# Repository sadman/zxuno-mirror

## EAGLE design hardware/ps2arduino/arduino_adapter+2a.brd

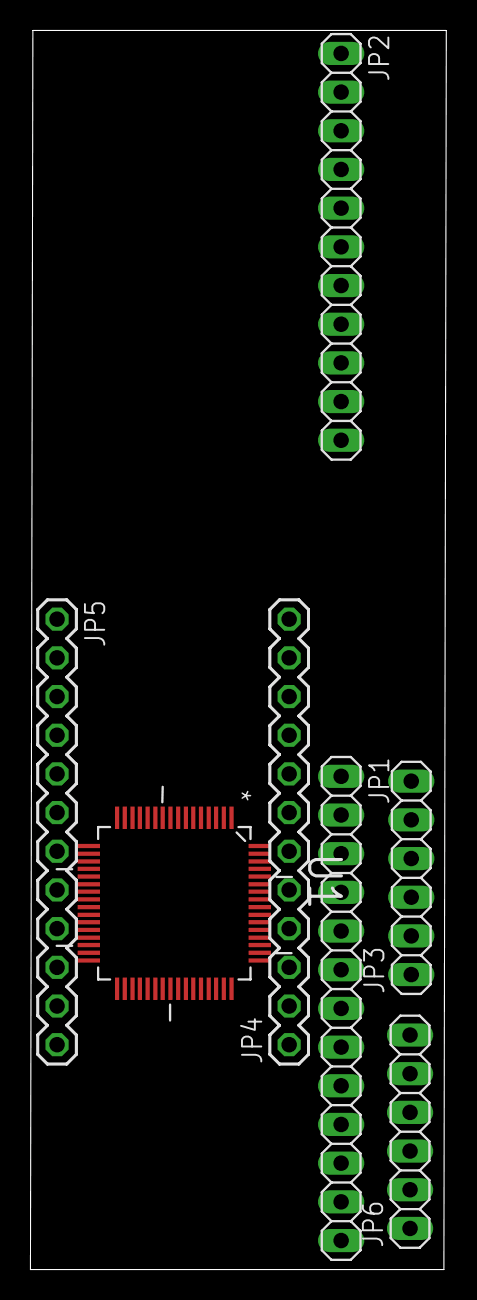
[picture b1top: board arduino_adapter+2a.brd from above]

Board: 2 copper layers, 27.3 x 81.4 mm, 7 parts (0 on the bottom side), 19 nets, no tracks yet.

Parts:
JP1: 1X13
JP2: 1X11
JP3, JP6: 1X06
JP4, JP5: 1X12
U1: STM32F105RBT6; QFP50P1200X1200X160-64N

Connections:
A8: JP1.6, JP4.3
A9: JP1.3, JP4.6
A10: JP1.2, JP4.7
A11: JP1.1, JP4.8
A12: JP1.4, JP4.5
A13: JP1.5, JP4.4
A14: JP1.7, JP4.2
A15: JP1.8, JP4.1
D0: JP2.1, JP5.7
D1: JP2.2, JP5.8
D2: JP2.3, JP5.10
D3: JP2.4, JP5.11
D4: JP2.5, JP5.12
GND: JP3.3, JP5.2, JP6.3
unnamed: JP3.6, JP6.5
unnamed: JP3.2, JP6.1
PS2_CLK: JP3.5, JP5.6
PS2_DATA: JP3.1, JP5.5
VCC: JP3.4, JP5.1, JP6.4

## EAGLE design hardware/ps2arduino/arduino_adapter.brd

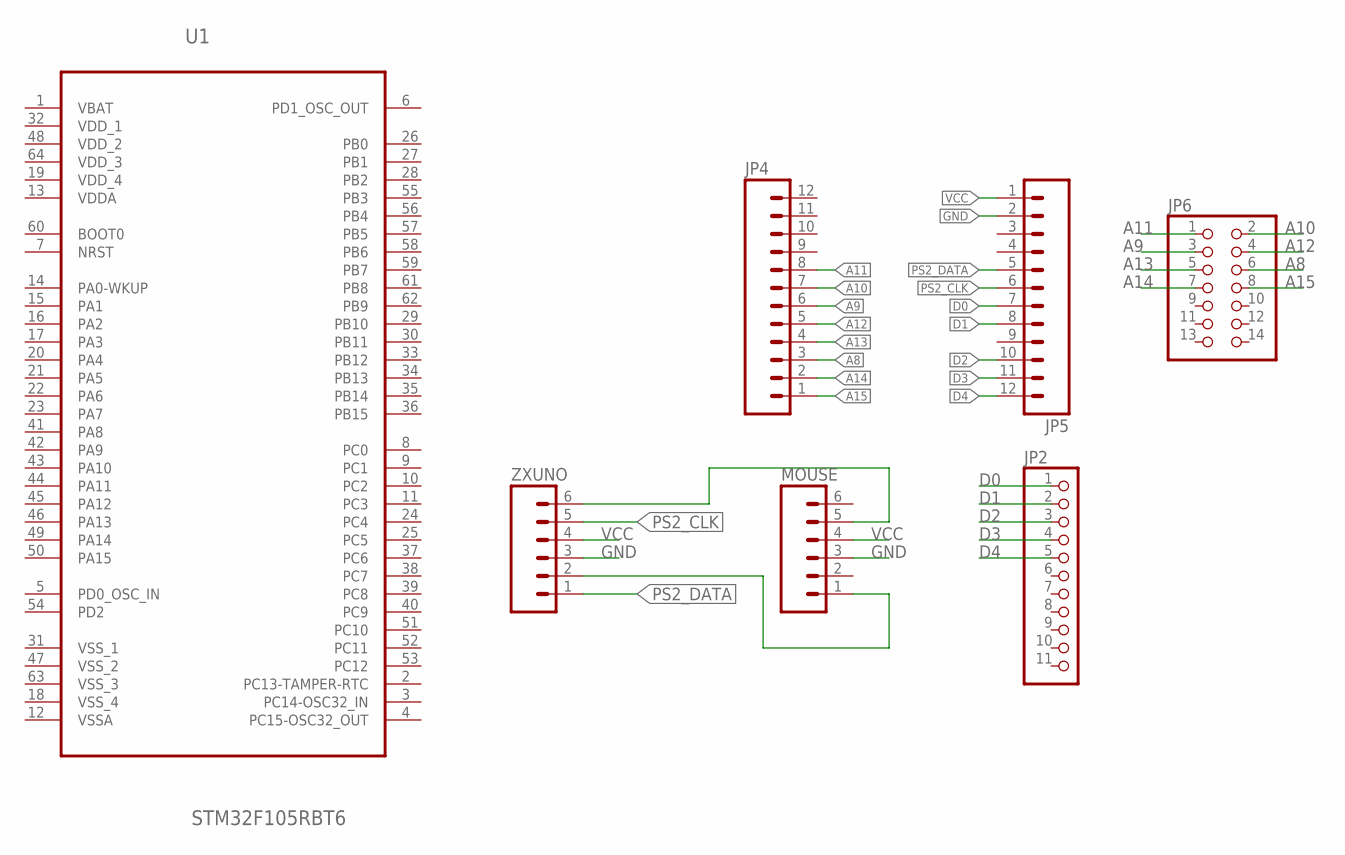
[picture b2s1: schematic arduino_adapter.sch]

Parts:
JP2: PINHD-1X11; 1X11
JP4, JP5: M12PTH; 1X12
JP6: PINHD-2X7; 2X07
MOUSE: DINC_MIN_TM_6_1; DINC/MIN_TM/6_1PRIMARY
U1: STM32F105RBT6; QFP50P1200X1200X160-64N
ZXUNO: DINC_MIN_TM_6_1; DINC/MIN_TM/6_1PRIMARY

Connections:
A8: JP4.3, JP6.6
A9: JP4.6, JP6.3
A10: JP4.7, JP6.2
A11: JP4.8, JP6.1
A12: JP4.5, JP6.4
A13: JP4.4, JP6.5
A14: JP4.2, JP6.7
A15: JP4.1, JP6.8
D0: JP2.1, JP5.7
D1: JP2.2, JP5.8
D2: JP2.3, JP5.10
D3: JP2.4, JP5.11
D4: JP2.5, JP5.12
GND: JP5.2, MOUSE.3, ZXUNO.3
unnamed: MOUSE.5, ZXUNO.6
unnamed: MOUSE.1, ZXUNO.2
PS2_CLK: JP5.6, ZXUNO.5
PS2_DATA: JP5.5, ZXUNO.1
VBAT: U1.1 (VBAT)
VCC: JP5.1, MOUSE.4, ZXUNO.4
VDDA: U1.13 (VDDA)
VDD_1: U1.32 (VDD_1)
VDD_2: U1.48 (VDD_2)
VDD_3: U1.64 (VDD_3)
VDD_4: U1.19 (VDD_4)
VSSA: U1.12 (VSSA)
VSS_1: U1.31 (VSS_1)
VSS_2: U1.47 (VSS_2)
VSS_3: U1.63 (VSS_3)
VSS_4: U1.18 (VSS_4)

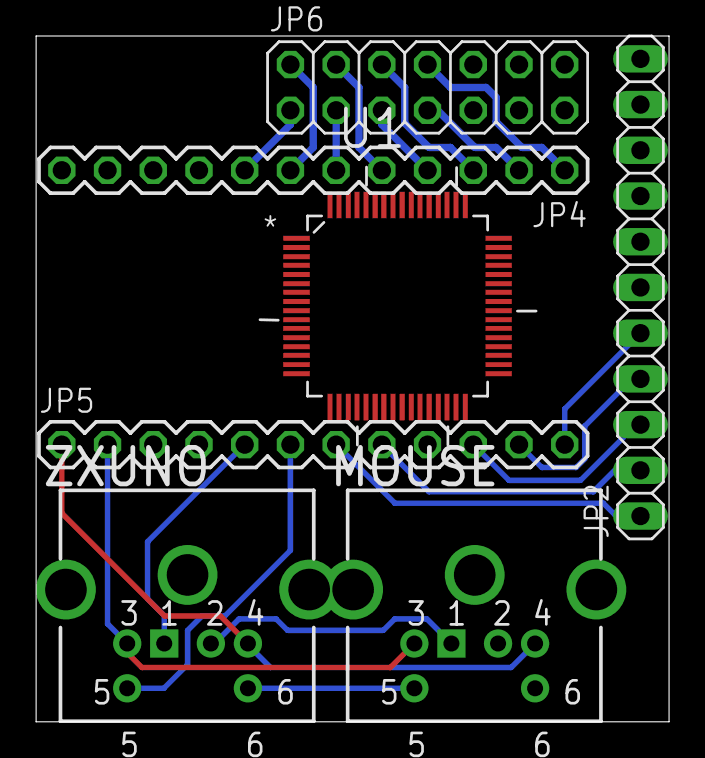
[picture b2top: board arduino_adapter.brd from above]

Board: 2 copper layers, 35.2 x 38.1 mm, 7 parts (0 on the bottom side), 19 nets.

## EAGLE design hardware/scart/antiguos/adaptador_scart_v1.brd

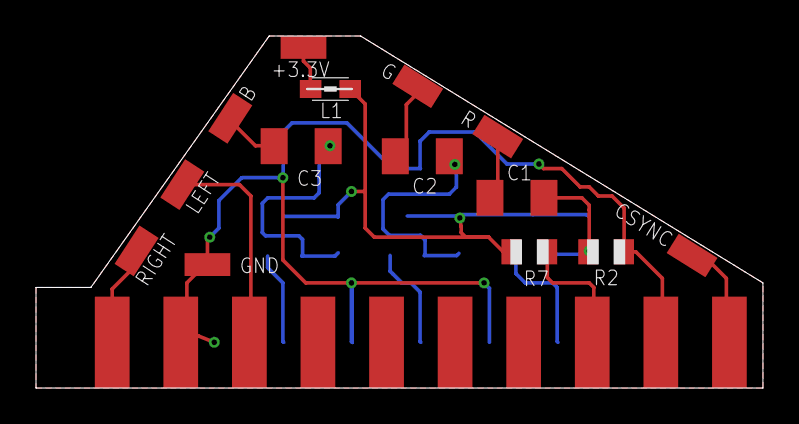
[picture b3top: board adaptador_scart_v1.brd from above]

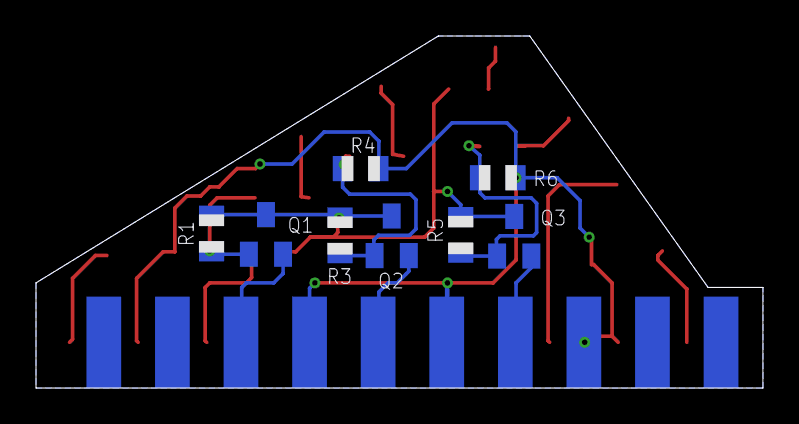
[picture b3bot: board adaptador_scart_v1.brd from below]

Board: 2 copper layers, 40.4 x 19.6 mm, 23 parts (9 on the bottom side), 16 nets.

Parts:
+3.3V: SMD1,27-2,54
B: SMD1,27-2,54
C1, C2, C3: 1uF; C1206K
CSYNC: SMD1,27-2,54
G: SMD1,27-2,54
GND: SMD1,27-2,54
L1: 0805
LEFT: SMD1,27-2,54
Q1, Q2, Q3: 2N3904; SOT23
R: SMD1,27-2,54
R1, R3, R5: 10K; R0805
R2, R4, R6: 22K; R0805
R7: 50; R0805
RIGHT: SMD1,27-2,54
U$1: SCART-MALE-PCB; SCART-PCB

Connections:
BIN: B.1, C3.1
BOUT: Q3.2, U$1.7
CSYNC: CSYNC.1, U$1.20
FS: R7.1, U$1.16
GIN: C2.1, G.1
GND: GND.1, R2.1, R4.1, R6.1, U$1.4, U$1.5, U$1.9, U$1.13, U$1.18
GOUT: Q2.2, U$1.11
LEFT: LEFT.1, U$1.6
unnamed: C1.2, Q1.1, R1.1, R2.2
unnamed: C3.2, Q3.1, R5.1, R6.2
unnamed: C2.2, Q2.1, R3.1, R4.2
RIGHT: RIGHT.1, U$1.2
RIN: C1.1, R.1
ROUT: Q1.2, U$1.15
VCC: L1.2, Q1.3, Q2.3, Q3.3, R1.2, R3.2, R5.2, R7.2
VCCIN: +3.3V.1, L1.1

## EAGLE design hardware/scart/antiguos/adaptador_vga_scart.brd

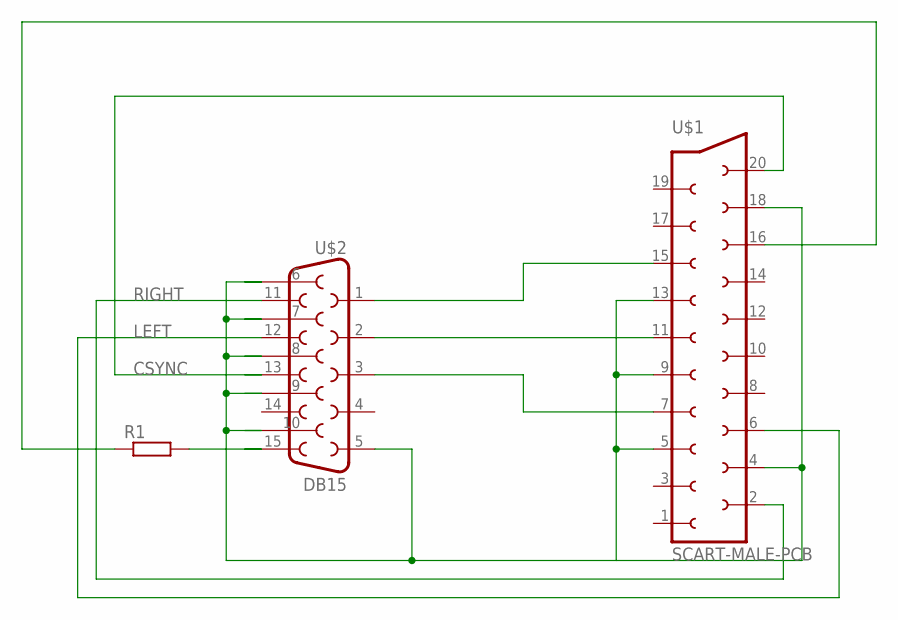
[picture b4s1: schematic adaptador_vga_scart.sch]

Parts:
R1: R-EU_0204/7; 0204/7
U$1: SCART-MALE-PCB; SCART-PCB
U$2: DB15

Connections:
BOUT: U$1.7, U$2.3
CSYNC: U$1.20, U$2.13
GND: U$1.4, U$1.5, U$1.9, U$1.13, U$1.18, U$2.5, U$2.6, U$2.7, U$2.8, U$2.9, U$2.10
GOUT: U$1.11, U$2.2
LEFT: U$1.6, U$2.12
unnamed: U$1.15, U$2.1
unnamed: R1.2, U$2.15
unnamed: R1.1, U$1.16
RIGHT: U$1.2, U$2.11

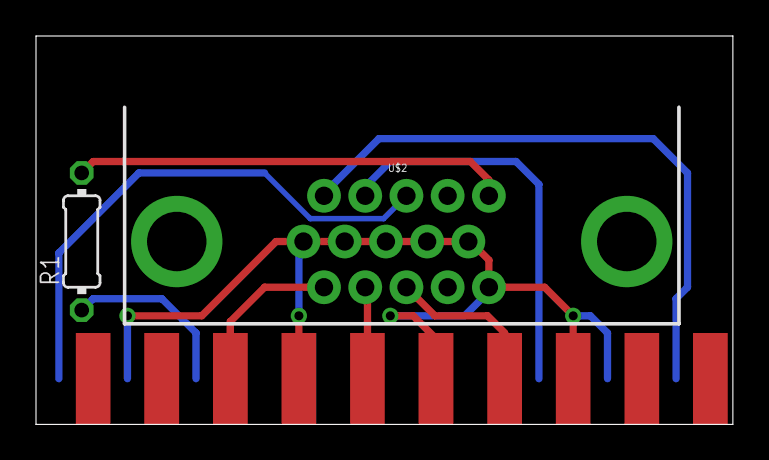
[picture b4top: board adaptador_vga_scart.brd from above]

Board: 2 copper layers, 38.7 x 21.6 mm, 3 parts (0 on the bottom side), 9 nets.

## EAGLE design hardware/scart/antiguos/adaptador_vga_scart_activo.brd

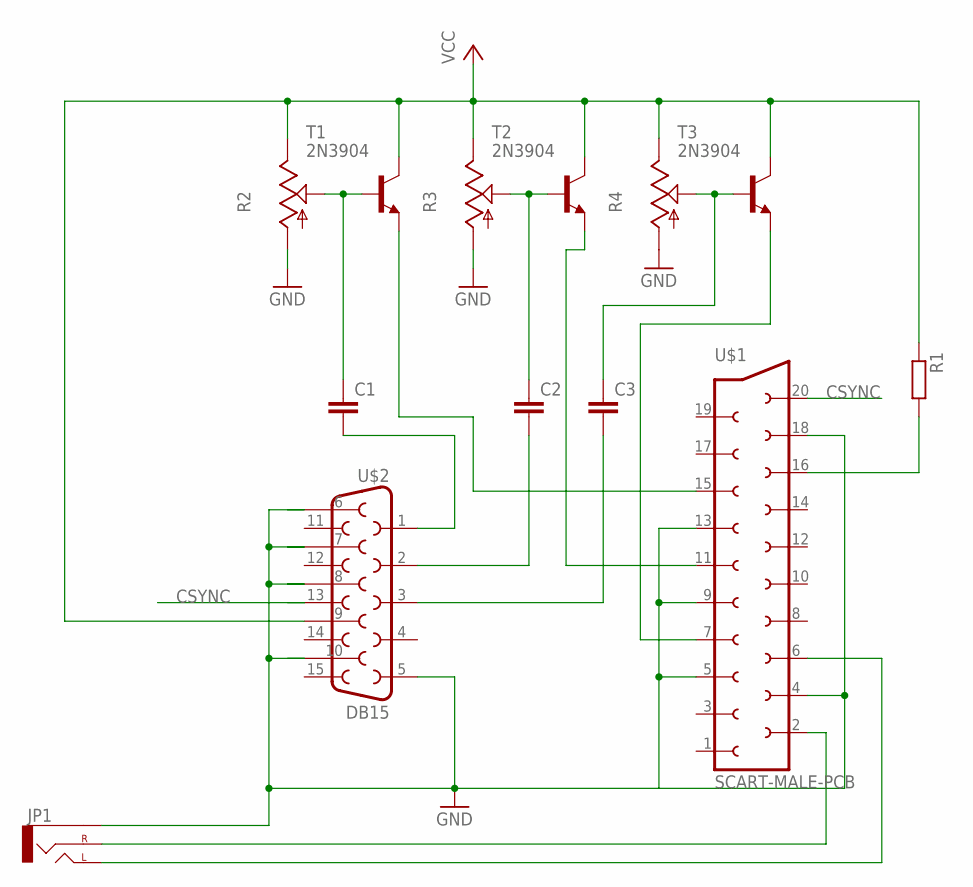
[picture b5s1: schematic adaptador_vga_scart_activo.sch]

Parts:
C1, C2, C3: C2,5-3; C2.5-3
JP1: AUDIO-JACKPTH; AUDIO-JACK
R1: R-EU_0204/5; 0204/5
R2, R3, R4: TRIM_US-CA6V; CA6V
T1, T2, T3: 2N3904; TO92
U$1: SCART-MALE-PCB; SCART-PCB
U$2: DB15

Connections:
BIN: C3.1, R4.S, T3.2 (B)
BOUT: T3.3 (E), U$1.7
CSYNC: U$1.20, U$2.13
GIN: C2.2, U$2.2
GND: JP1.SLEEVE, R2.A, R3.A, R4.A, U$1.4, U$1.5, U$1.9, U$1.13, U$1.18, U$2.5, U$2.6, U$2.7, U$2.8, U$2.10
GOUT: T2.3 (E), U$1.11
LEFT: JP1.TIP (LEFT), U$1.6
unnamed: C1.1, R2.S, T1.2 (B)
unnamed: C2.1, R3.S, T2.2 (B)
unnamed: C3.2, U$2.3
unnamed: R1.2, U$1.16
RIGHT: JP1.RING (RIGHT), U$1.2
RIN: C1.2, U$2.1
ROUT: T1.3 (E), U$1.15
VCC: R1.1, R2.E, R3.E, R4.E, T1.1 (C), T2.1 (C), T3.1 (C), U$2.9

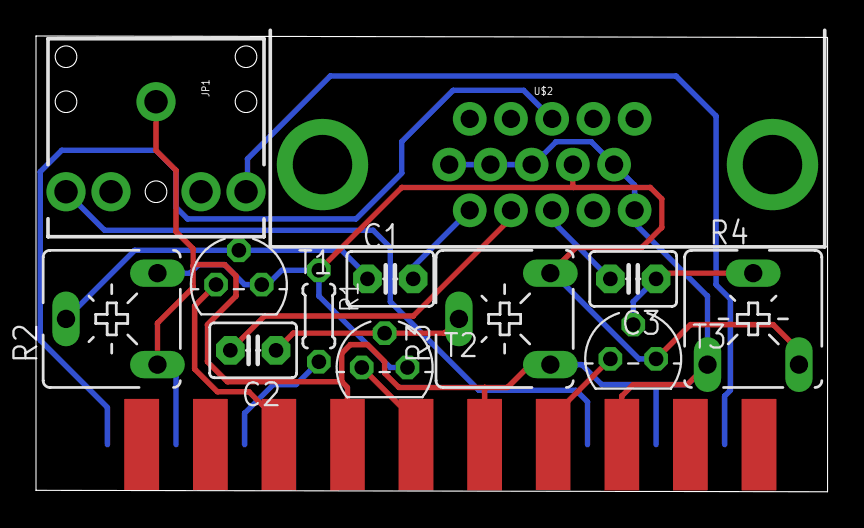
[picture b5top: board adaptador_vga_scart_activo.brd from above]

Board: 2 copper layers, 44.0 x 25.3 mm, 13 parts (0 on the bottom side), 15 nets.

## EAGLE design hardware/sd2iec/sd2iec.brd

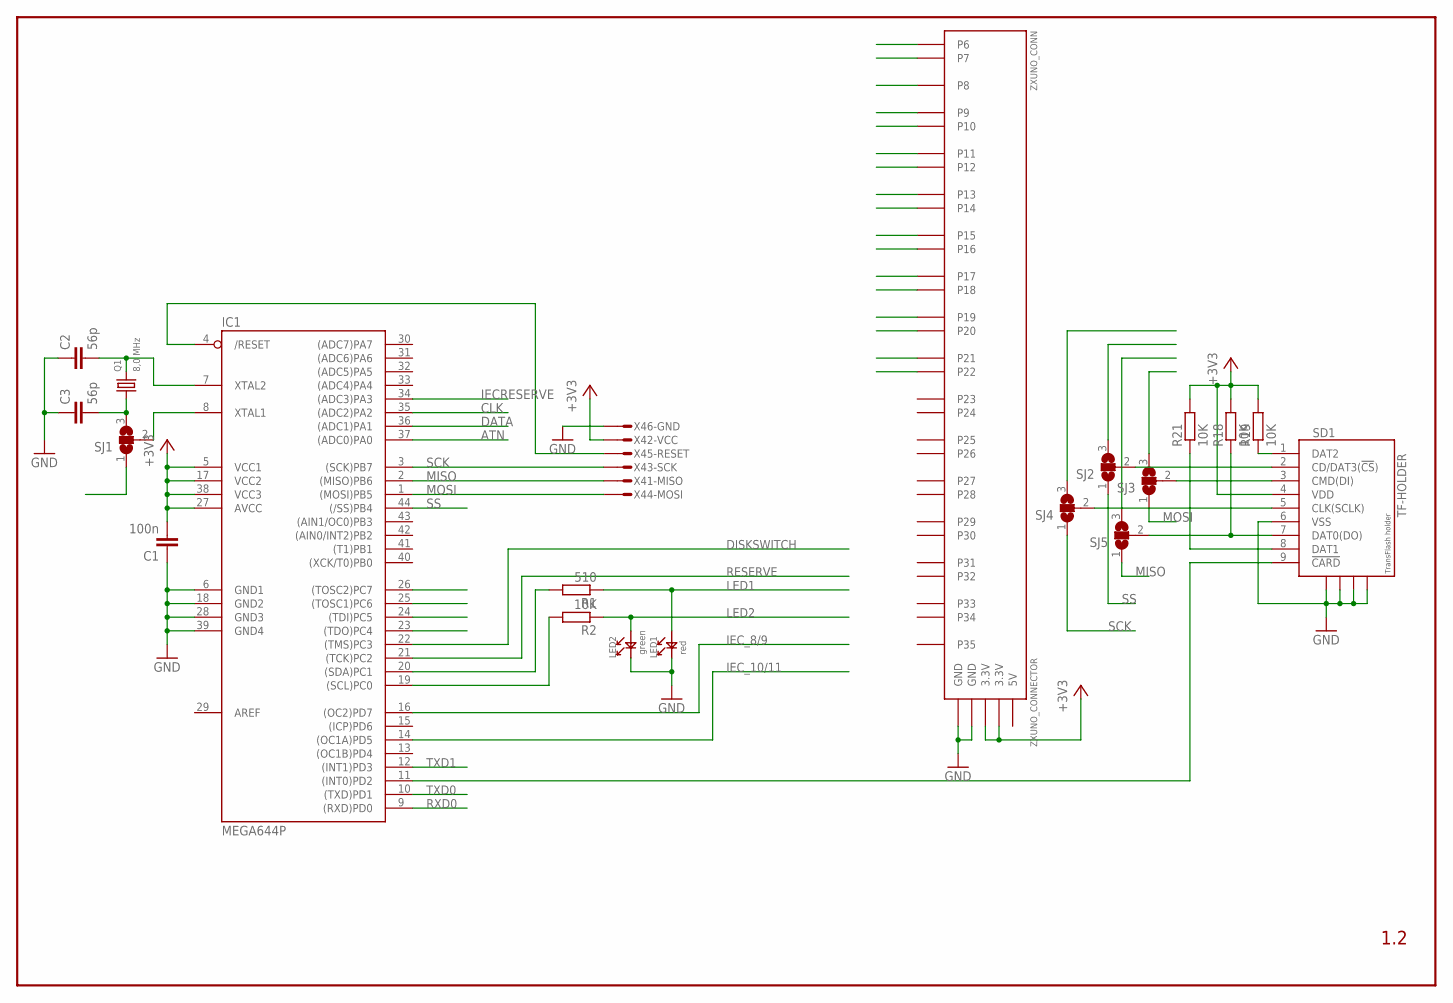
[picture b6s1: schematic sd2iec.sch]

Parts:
C1: 100n; C0805
C2, C3: 56p; C0805
IC1: MEGA644P; TQFP44
LED1: red; LED0805
LED2: green; LED0805
Q1: 8,0 MHz; HC49/S
R1: 510; R0805
R2, R18, R19, R21: 10K; R0805
SD1: TF-HOLDER; TF-PULL
SJ1, SJ2, SJ3, SJ4, SJ5: SJ2W; SJ_2
X4: AVR-ISP_1X6; 1X6_ISP
ZXUNO_CONN: ZXUNO_CONNECTOR

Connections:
5V: ZXUNO_CONN.5V
+3V3: C1.2, IC1.5 (VCC1), IC1.17 (VCC2), IC1.27 (AVCC), IC1.38 (VCC3), R18.2, R19.2, R21.2, SD1.4 (VDD), X4.2, ZXUNO_CONN.3.3V@1 (3.3V), ZXUNO_CONN.3.3V@2 (3.3V)
/RESET: IC1.4 (/RESET), X4.5
ATN: IC1.37 ((ADC0)PA0)
CD: IC1.11 ((INT0)PD2), SD1.9 (!CARD)
CLK: IC1.35 ((ADC2)PA2)
DATA: IC1.36 ((ADC1)PA1)
DISKSWITCH: IC1.22 ((TMS)PC3)
GND: C1.1, C2.1, C3.1, IC1.6 (GND1), IC1.18 (GND2), IC1.28 (GND3), IC1.39 (GND4), LED1.1, LED2.1, SD1.6 (VSS), SD1.S1, SD1.S2, SD1.S3, SD1.S4, X4.6, ZXUNO_CONN.GND@1 (GND), ZXUNO_CONN.GND@2 (GND)
IECRESERVE: IC1.34 ((ADC3)PA3)
IEC_8/9: IC1.16 ((OC2)PD7)
IEC_10/11: IC1.14 ((OC1A)PD5)
LED1: LED1.2, R1.1
LED2: LED2.2, R2.1
MISO: IC1.2 ((MISO)PB6), SJ5.1, X4.1
MOSI: IC1.1 ((MOSI)PB5), SJ3.1, X4.4
unnamed: R18.1, SD1.7 (DAT0(DO)), SJ5.2
unnamed: SD1.3 (CMD(DI)), SJ3.2
unnamed: C3.2, Q1.1, SJ1.3
unnamed: C2.2, IC1.7 (XTAL2), Q1.2
unnamed: SD1.2 (CD/DAT3(!CS!)), SJ2.2
unnamed: IC1.8 (XTAL1), SJ1.2
unnamed: R19.1, SD1.1 (DAT2)
unnamed: SD1.5 (CLK(SCLK)), SJ4.2
unnamed: R21.1, SD1.8 (DAT1)
P6: ZXUNO_CONN.P6
P7: ZXUNO_CONN.P7
P8: ZXUNO_CONN.P8
P9: ZXUNO_CONN.P9
P10: ZXUNO_CONN.P10
P11: ZXUNO_CONN.P11
P12: ZXUNO_CONN.P12
P13: ZXUNO_CONN.P13
P14: ZXUNO_CONN.P14
P15: ZXUNO_CONN.P15
P16: ZXUNO_CONN.P16
P17: ZXUNO_CONN.P17
P18: ZXUNO_CONN.P18
P19: ZXUNO_CONN.P19
P20: ZXUNO_CONN.P20
P21: ZXUNO_CONN.P21
P22: ZXUNO_CONN.P22
PC0: IC1.19 ((SCL)PC0), R2.2
PC1: IC1.20 ((SDA)PC1), R1.2
RESERVE: IC1.21 ((TCK)PC2)
RXD0: IC1.9 ((RXD)PD0)
SCK: IC1.3 ((SCK)PB7), SJ4.1, X4.3
SS: IC1.44 ((/SS)PB4), SJ2.1
TXD0: IC1.10 ((TXD)PD1)
TXD1: IC1.12 ((INT1)PD3)

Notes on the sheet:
1.2

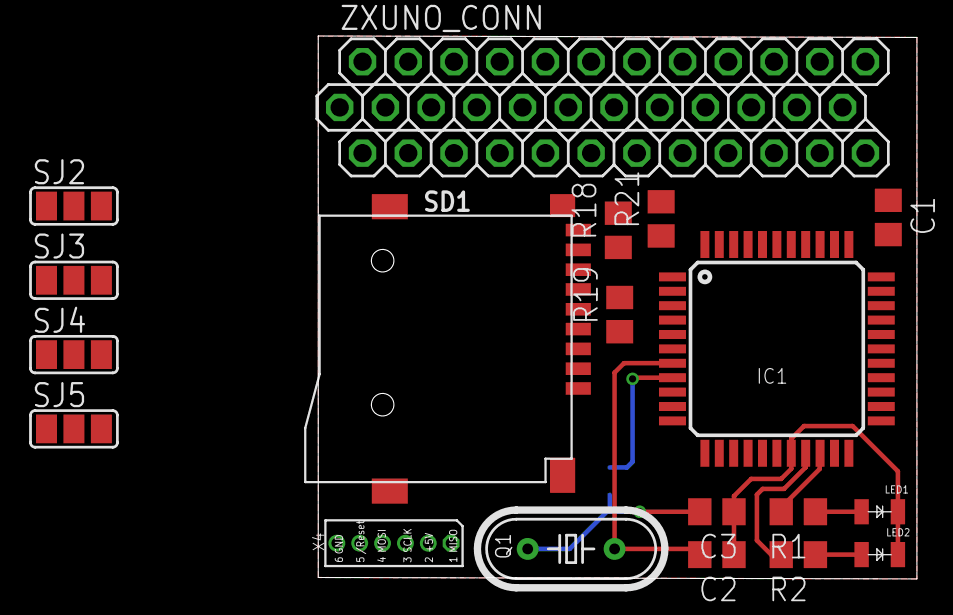
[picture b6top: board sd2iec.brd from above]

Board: 2 copper layers, 33.3 x 30.2 mm, 20 parts (1 on the bottom side), 21 nets.

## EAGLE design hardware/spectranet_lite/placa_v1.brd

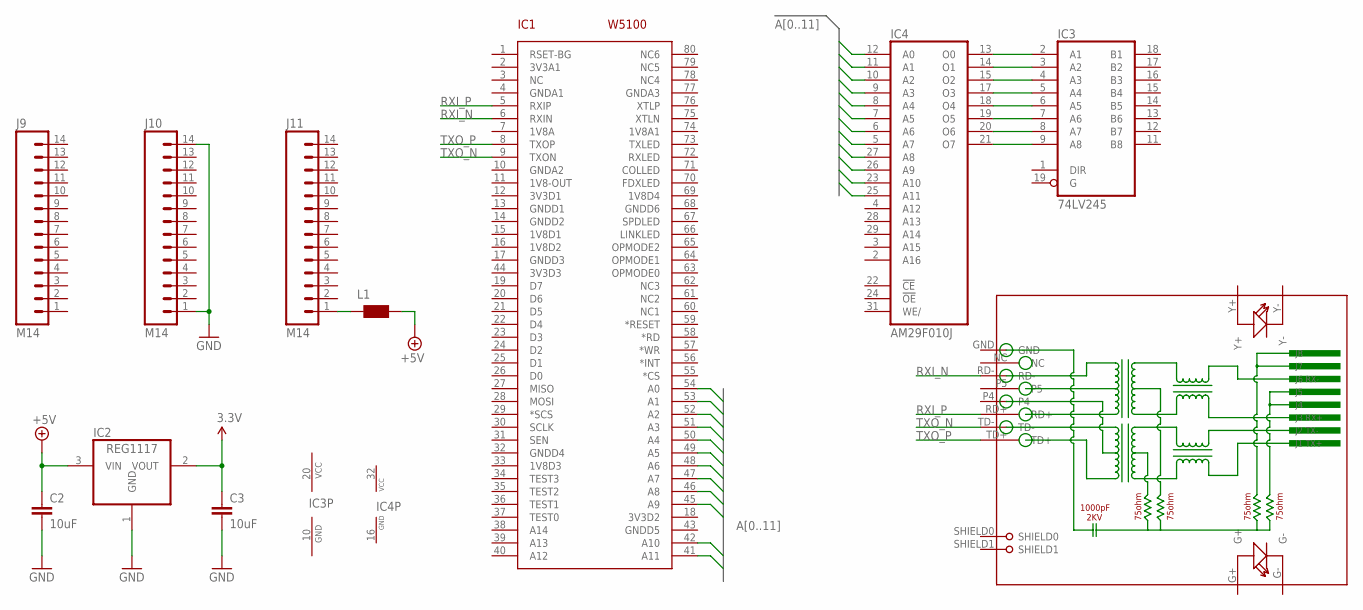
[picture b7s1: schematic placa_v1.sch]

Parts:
C2, C3: 10uF; C0805K
IC1: W5100; SQFP-S-10X10-80
IC2: REG1117; SOT223
IC3: 74LV245; SO20W
IC4: AM29F010J; PLCC32R
J9, J10, J11: M14; 1X14
L1: WE-CBF_0805; 0805
RJ1: HR911105A

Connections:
1V8-OUT: IC1.11 (1V8-OUT)
1V8A: IC1.7 (1V8A)
1V8A1: IC1.74 (1V8A1)
1V8D1: IC1.15 (1V8D1)
1V8D2: IC1.16 (1V8D2)
1V8D3: IC1.33 (1V8D3)
1V8D4: IC1.69 (1V8D4)
3.3V: C3.1, IC2.2 (VOUT)
3V3A1: IC1.2 (3V3A1)
3V3D1: IC1.12 (3V3D1)
3V3D2: IC1.18 (3V3D2)
3V3D3: IC1.44 (3V3D3)
+5V: C2.1, IC2.3 (VIN), L1.2
A0: IC1.54 (A0), IC4.12 (A0)
A1: IC1.53 (A1), IC4.11 (A1)
A2: IC1.52 (A2), IC4.10 (A2)
A3: IC1.51 (A3), IC4.9 (A3)
A4: IC1.50 (A4), IC4.8 (A4)
A5: IC1.49 (A5), IC4.7 (A5)
A6: IC1.48 (A6), IC4.6 (A6)
A7: IC1.47 (A7), IC4.5 (A7)
A8: IC1.46 (A8), IC4.27 (A8)
A9: IC1.45 (A9), IC4.26 (A9)
A10: IC1.42 (A10), IC4.23 (A10)
A11: IC1.41 (A11), IC4.25 (A11)
GND: C2.2, C3.2, IC2.1 (GND), IC3.10 (GND), IC4.16 (GND), J10.1, J10.14
GNDA1: IC1.4 (GNDA1)
GNDA2: IC1.10 (GNDA2)
GNDA3: IC1.77 (GNDA3)
GNDD1: IC1.13 (GNDD1)
GNDD2: IC1.14 (GNDD2)
GNDD3: IC1.17 (GNDD3)
GNDD4: IC1.32 (GNDD4)
GNDD5: IC1.43 (GNDD5)
GNDD6: IC1.68 (GNDD6)
unnamed: J11.1, L1.1
unnamed: IC3.2 (A1), IC4.13 (O0)
unnamed: IC3.3 (A2), IC4.14 (O1)
unnamed: IC3.4 (A3), IC4.15 (O2)
unnamed: IC3.5 (A4), IC4.17 (O3)
unnamed: IC3.6 (A5), IC4.18 (O4)
unnamed: IC3.7 (A6), IC4.19 (O5)
unnamed: IC3.8 (A7), IC4.20 (O6)
unnamed: IC3.9 (A8), IC4.21 (O7)
RXI_N: IC1.6 (RXIN), RJ1.RD-
RXI_P: IC1.5 (RXIP), RJ1.RD+
TXO_N: IC1.9 (TXON), RJ1.TD-
TXO_P: IC1.8 (TXOP), RJ1.TD+
VCC: IC3.20 (VCC), IC4.32 (VCC)

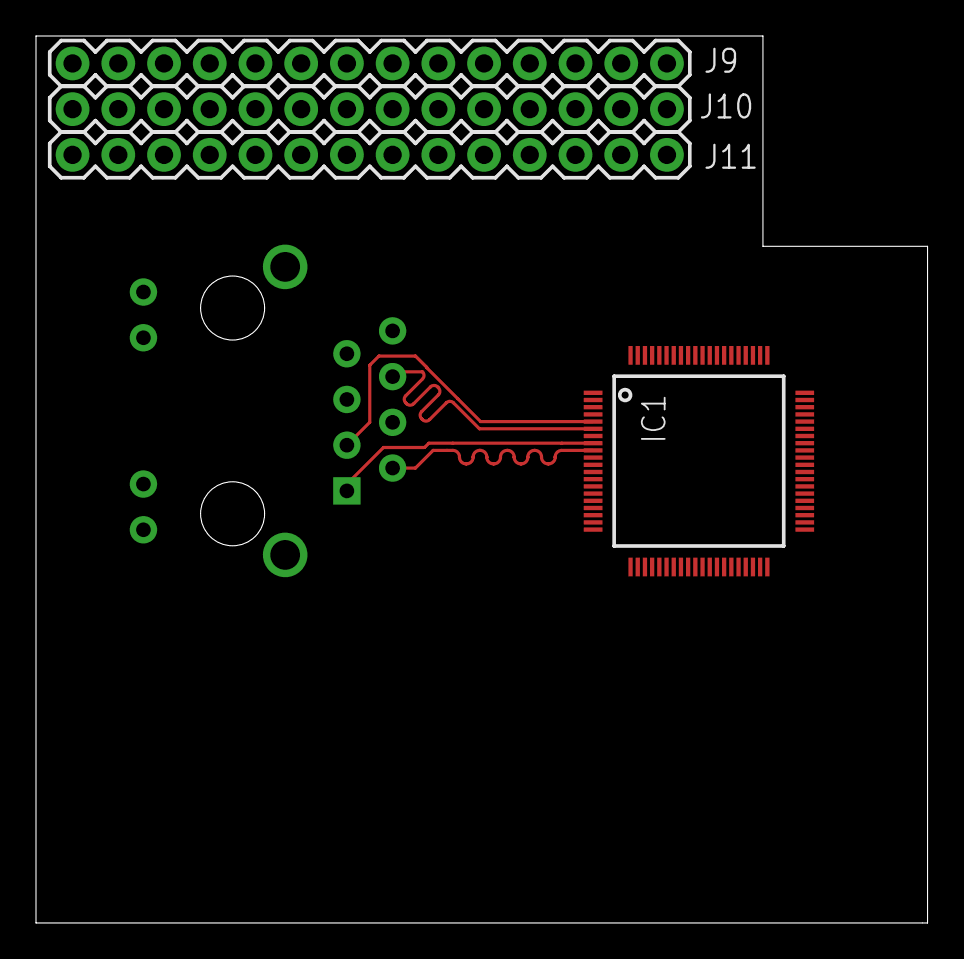
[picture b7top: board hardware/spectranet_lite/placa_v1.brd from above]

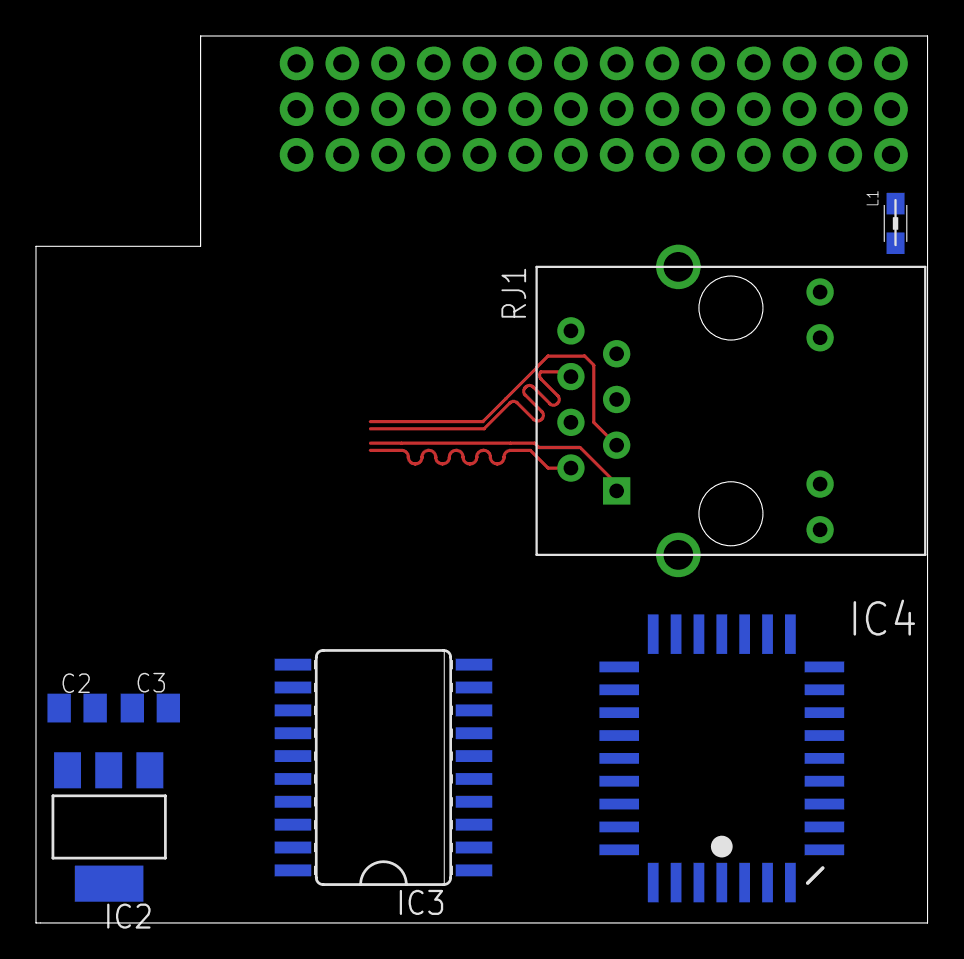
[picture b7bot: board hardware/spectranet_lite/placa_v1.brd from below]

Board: 2 copper layers, 49.5 x 49.3 mm, 11 parts (7 on the bottom side), 29 nets.

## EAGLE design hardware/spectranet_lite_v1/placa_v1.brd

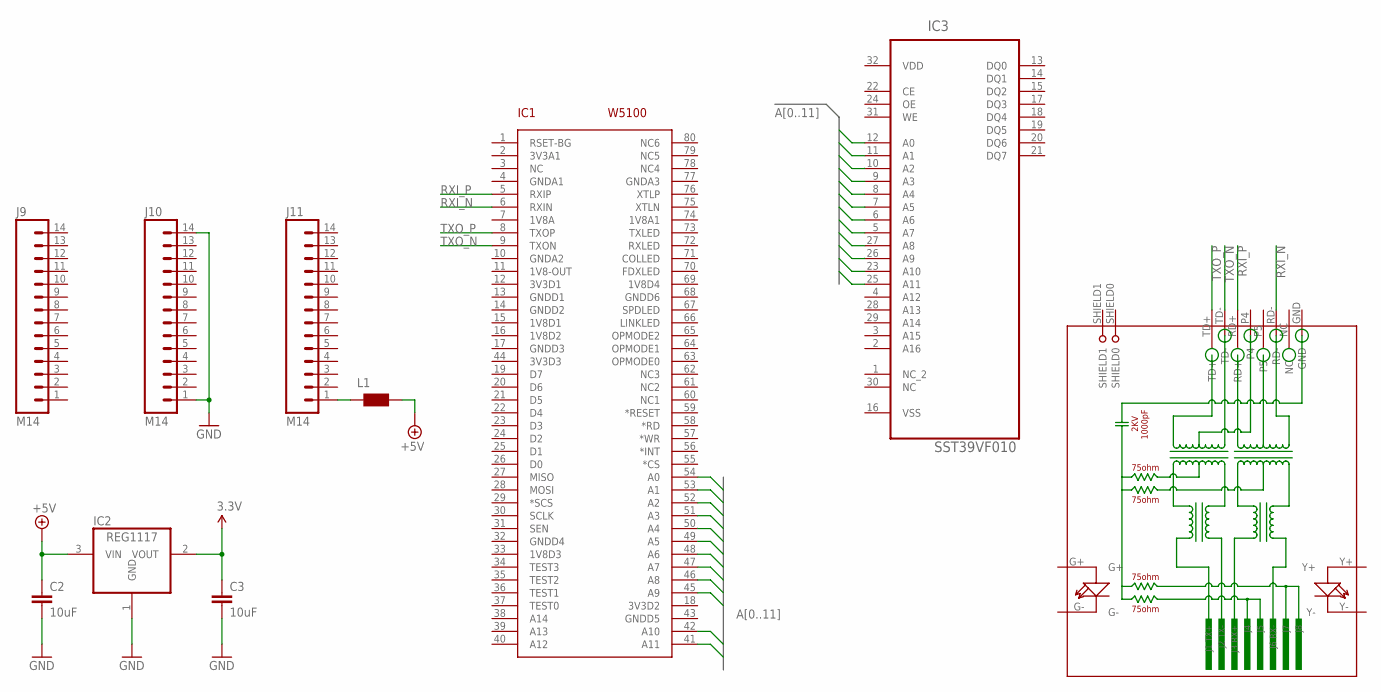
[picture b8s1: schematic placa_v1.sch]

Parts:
C2, C3: 10uF; C0805K
IC1: W5100; SQFP-S-10X10-80
IC2: REG1117; SOT223
IC3: SST39VF010; PLCC127P1244X1498X357-32N
J9, J10, J11: M14; 1X14
L1: WE-CBF_0805; 0805
RJ1: HR911105A

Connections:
1V8-OUT: IC1.11 (1V8-OUT)
1V8A: IC1.7 (1V8A)
1V8A1: IC1.74 (1V8A1)
1V8D1: IC1.15 (1V8D1)
1V8D2: IC1.16 (1V8D2)
1V8D3: IC1.33 (1V8D3)
1V8D4: IC1.69 (1V8D4)
3.3V: C3.1, IC2.2 (VOUT)
3V3A1: IC1.2 (3V3A1)
3V3D1: IC1.12 (3V3D1)
3V3D2: IC1.18 (3V3D2)
3V3D3: IC1.44 (3V3D3)
+5V: C2.1, IC2.3 (VIN), L1.2
A0: IC1.54 (A0), IC3.12 (A0)
A1: IC1.53 (A1), IC3.11 (A1)
A2: IC1.52 (A2), IC3.10 (A2)
A3: IC1.51 (A3), IC3.9 (A3)
A4: IC1.50 (A4), IC3.8 (A4)
A5: IC1.49 (A5), IC3.7 (A5)
A6: IC1.48 (A6), IC3.6 (A6)
A7: IC1.47 (A7), IC3.5 (A7)
A8: IC1.46 (A8), IC3.27 (A8)
A9: IC1.45 (A9), IC3.26 (A9)
A10: IC1.42 (A10), IC3.23 (A10)
A11: IC1.41 (A11), IC3.25 (A11)
GND: C2.2, C3.2, IC2.1 (GND), J10.1, J10.14
GNDA1: IC1.4 (GNDA1)
GNDA2: IC1.10 (GNDA2)
GNDA3: IC1.77 (GNDA3)
GNDD1: IC1.13 (GNDD1)
GNDD2: IC1.14 (GNDD2)
GNDD3: IC1.17 (GNDD3)
GNDD4: IC1.32 (GNDD4)
GNDD5: IC1.43 (GNDD5)
GNDD6: IC1.68 (GNDD6)
unnamed: J11.1, L1.1
RXI_N: IC1.6 (RXIN), RJ1.RD-
RXI_P: IC1.5 (RXIP), RJ1.RD+
TXO_N: IC1.9 (TXON), RJ1.TD-
TXO_P: IC1.8 (TXOP), RJ1.TD+
VDD: IC3.32 (VDD)

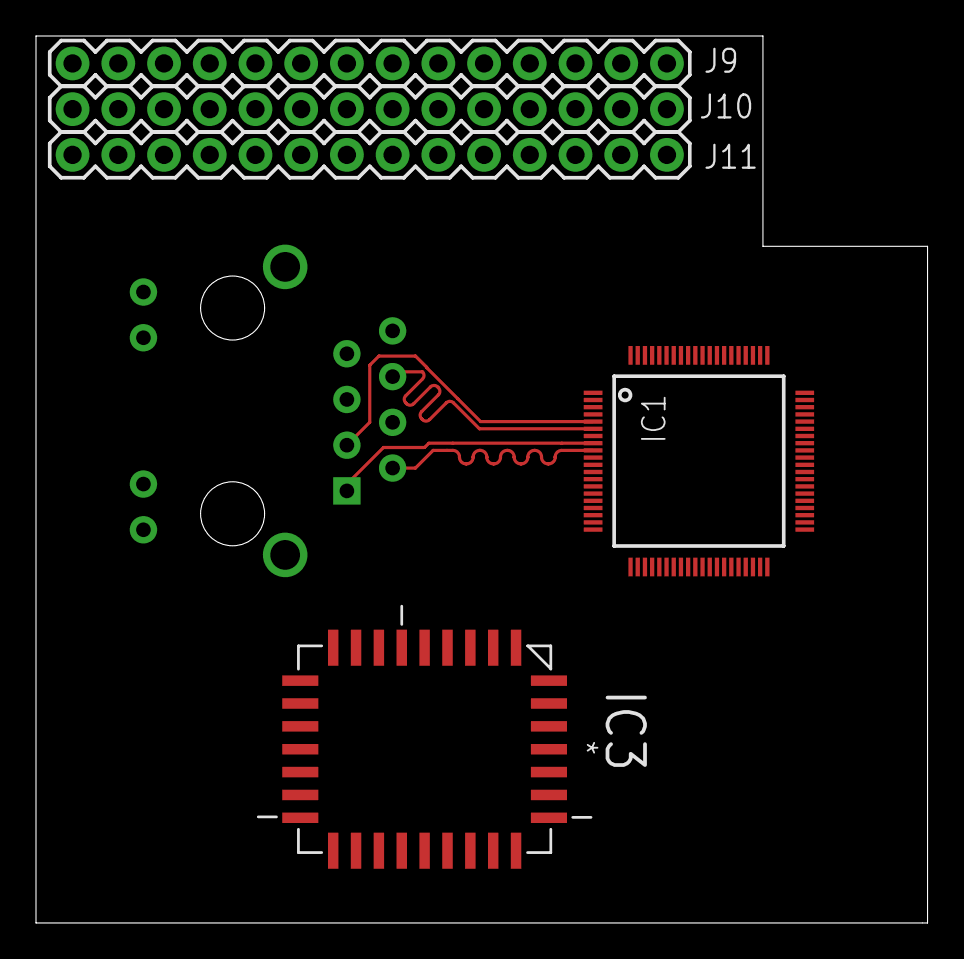
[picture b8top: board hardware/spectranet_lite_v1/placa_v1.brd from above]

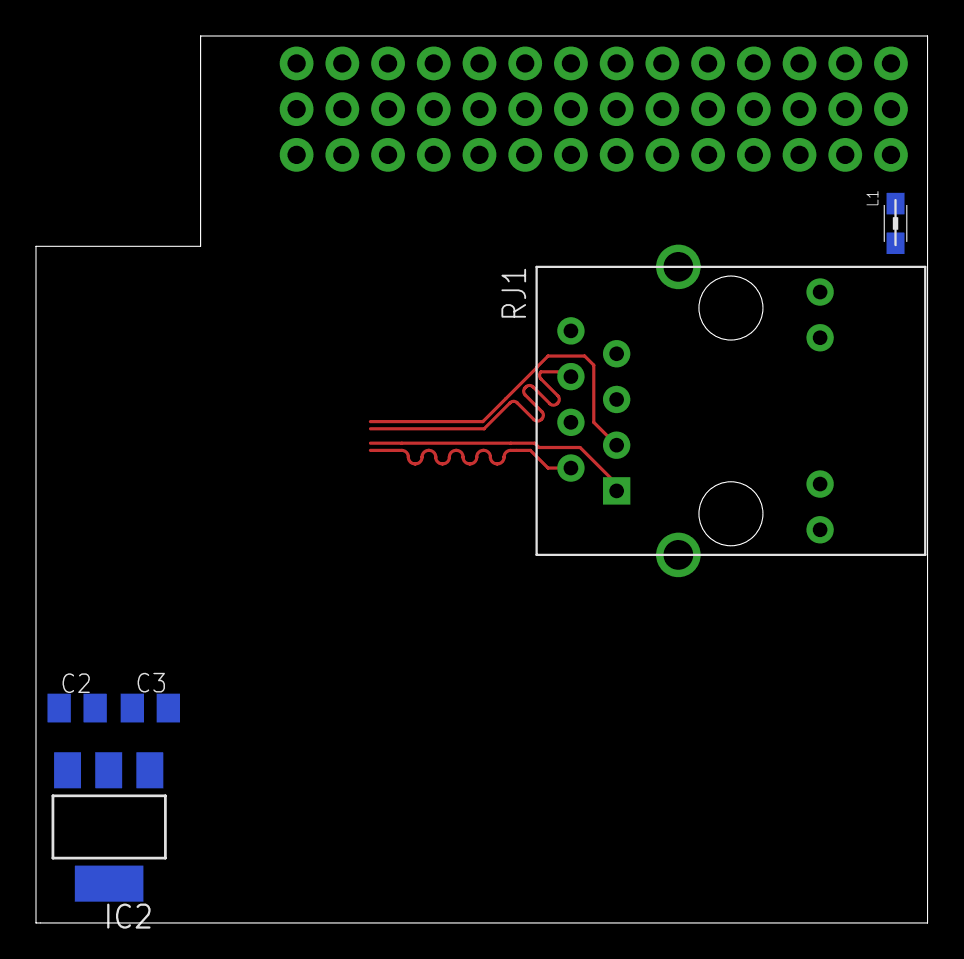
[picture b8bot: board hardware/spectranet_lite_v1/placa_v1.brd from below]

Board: 2 copper layers, 49.5 x 49.3 mm, 10 parts (5 on the bottom side), 20 nets.

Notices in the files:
parts and their libraries:
SparkFun-Connectors: Licensing: Creative Commons ShareAlike 4.0 International - https://creativecommons.org/licenses/by-sa/4.0
wuerth-elektronik: Copyright: Würth Elektronik eiSos
